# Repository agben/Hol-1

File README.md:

**HOL-1 a homebrew 8-bit TTL CPU**
---
HOL-1 is a TTL based 8-bit CPU based on the 'simple as possible' breadboard design by Ben Eater https://eater.net/8bit/

As well as adding my own modifications to each module of this CPU. i.e.
- more memory
- more registers
- more ALU functions
- more commands (assembler code to follow)

The main change is that HOL-1 is designed for permanent construction using common 8cm x 12cm double-sided perfboards.
  
For more on HOL-1 see www.benningtons.net  
  
**Design Principles**
---
- A working CPU is more important than performance or perfection (I'm learning as I go!)
- Using basic TTL 74LS family IC's from circa mid-70's. i.e. an ALU on one chip would be easier but where's the learning in that
- 8cm x 12cm double-sided perfboards = a 30 x 42 grid of 2.54mm spaced vias
- Initial design is on Fritzing (better suited to perfboard layouts but not suitable for Git)
- KiCad is then used for a more professional(ish) schematic and PCB design (and a more suitable format for Git)
- The KiCad PCB will adhere to the perfboard grid layout for component placement but tracks will then use a finer grid. This is because I'm not making PCBs but mass wiring the perfboard in wirewrapping style.
- Blinkenlights - plug-in status LEDs at every opportunity that could be swapped for control panel fly leads in the future

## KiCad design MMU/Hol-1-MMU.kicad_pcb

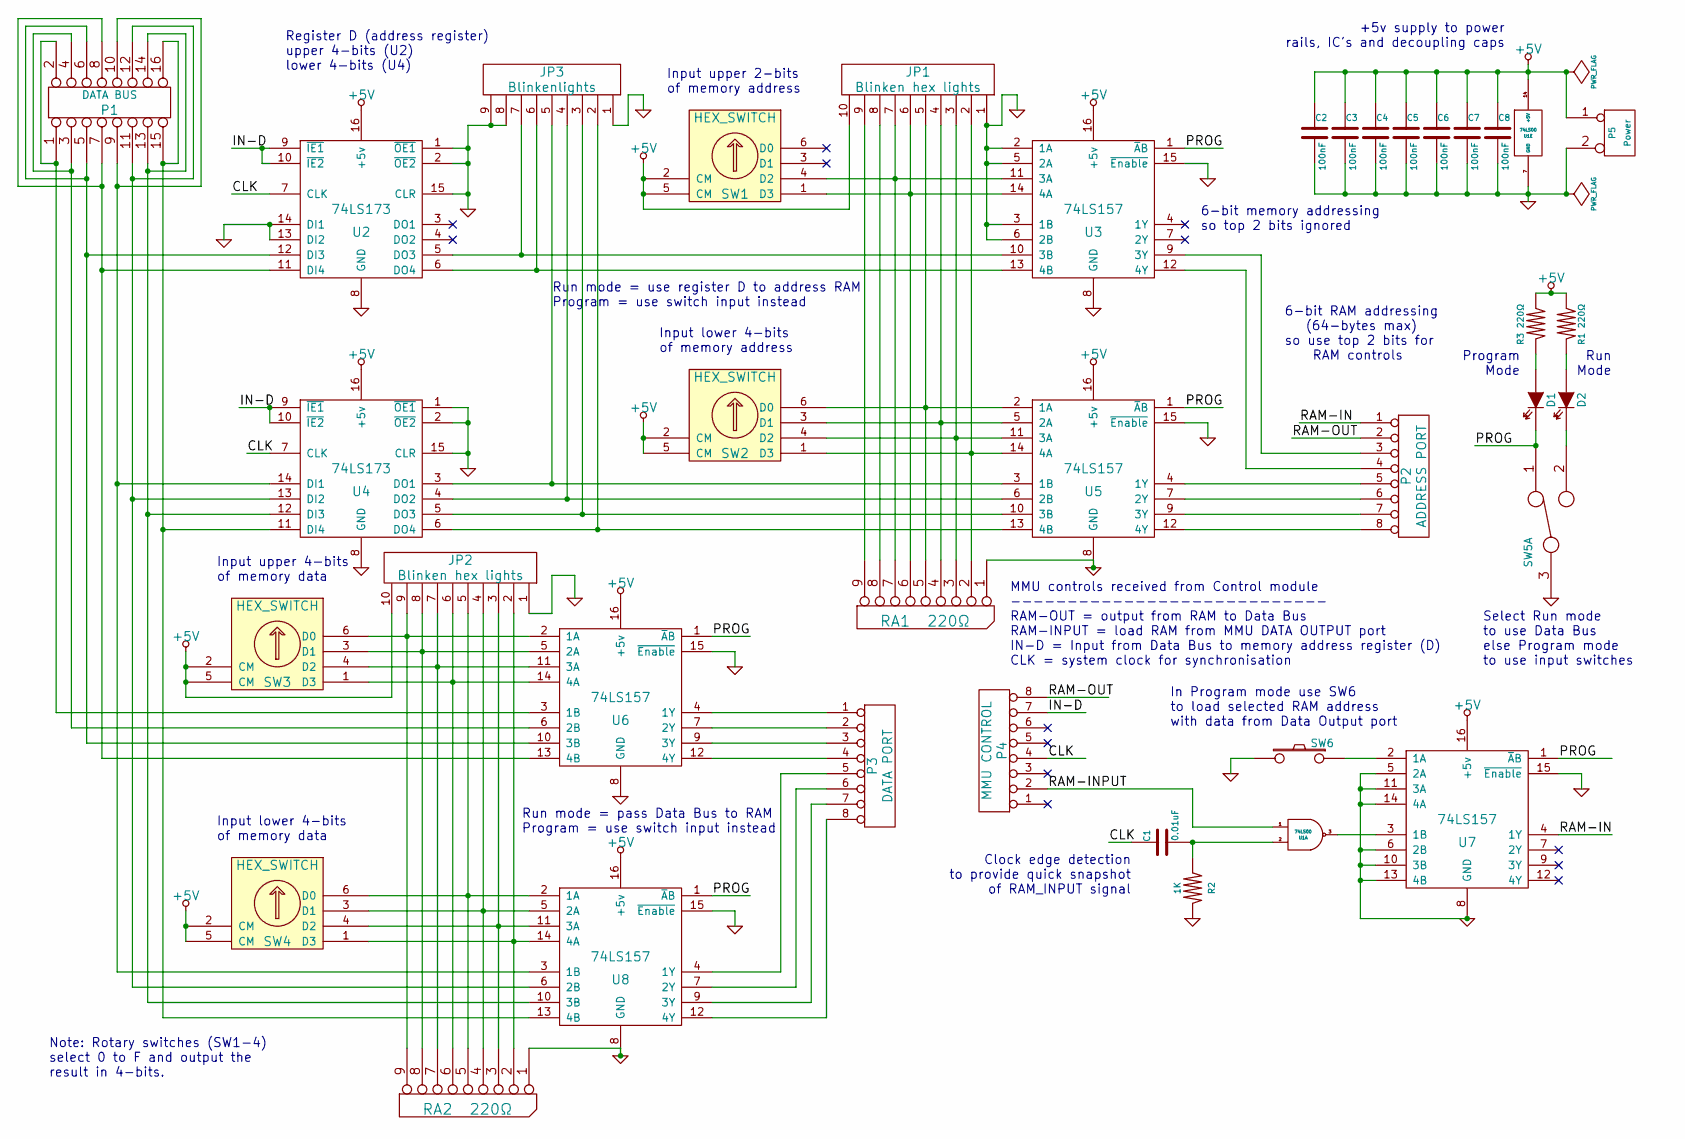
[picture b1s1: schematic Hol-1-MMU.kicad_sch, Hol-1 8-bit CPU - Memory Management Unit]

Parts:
C1: 0.01uF
C2, C3, C4, C5, C6, C7, C8: 100nF
D1, D2: LED
JP1, JP2: Blinken hex lights
JP3: Blinkenlights
P1: DATA BUS
P2: ADDRESS PORT
P3: DATA PORT
P4: MMU CONTROL
P5: Power
R1, R3: 220Ω
R2: 1K
RA1, RA2: 220Ω
SW1, SW2, SW3, SW4: HEX_SWITCH
SW5: DPDT
SW6: SW_PUSH
U1: 74LS00
U2, U4: 74LS173
U3, U5, U6, U7, U8: 74LS157

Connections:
+5V: C2.1, C3.1, C4.1, C5.1, C6.1, C7.1, C8.1, JP1.10, JP2.10, P5.1, R1.1, R3.1, SW1.2 (CM), SW1.5 (CM), SW2.2 (CM), SW2.5 (CM), SW3.2 (CM), SW3.5 (CM), SW4.2 (CM), SW4.5 (CM), U1.14 (+5V), U2.16 (+5v), U3.16 (+5v), U4.16 (+5v), U5.16 (+5v), U6.16 (+5v), U7.16 (+5v), U8.16 (+5v)
/CLK: C1.1, P4.4, U2.7 (CLK), U4.7 (CLK)
/IN-D: P4.7, U2.9 (~IE1), U2.10 (~IE2), U4.9 (~IE1), U4.10 (~IE2)
/PROG: D1.2 (K), SW5.1, U3.1 (~AB), U5.1 (~AB), U6.1 (~AB), U7.1 (~AB), U8.1 (~AB)
/RAM-IN: P2.1, U7.4 (1Y)
/RAM-INPUT: P4.2, U1.1
/RAM-OUT: P2.2, P4.8
GND: C2.2, C3.2, C4.2, C5.2, C6.2, C7.2, C8.2, JP1.1, JP2.1, JP3.1, JP3.8, JP3.9, P5.2 (PM), R2.2, RA1.1 (COM), RA2.1 (COM), SW5.3, SW6.2, U1.7 (GND), U2.1 (~OE1), U2.2 (~OE2), U2.8 (GND), U2.13 (DI2), U2.14 (DI1), U2.15 (CLR), U3.2 (1A), U3.3 (1B), U3.5 (2A), U3.6 (2B), U3.8 (GND), U3.15 (~Enable), U4.1 (~OE1), U4.2 (~OE2), U4.8 (GND), U4.15 (CLR), U5.8 (GND), U5.15 (~Enable), U6.8 (GND), U6.15 (~Enable), U7.5 (2A), U7.6 (2B), U7.8 (GND), U7.10 (3B), U7.11 (3A), U7.13 (4B), U7.14 (4A), U7.15 (~Enable), U8.8 (GND), U8.15 (~Enable)
unnamed: P2.4, U3.12 (4Y)
unnamed: P2.3, U3.9 (3Y)
unnamed: P1.1, P1.2, U6.3 (1B)
unnamed: P2.5, U5.4 (1Y)
unnamed: D2.2 (K), SW5.2
unnamed: JP2.2, RA2.2, SW4.1 (D3), U8.14 (4A)
unnamed: D1.1 (A), R3.2
unnamed: D2.1 (A), R1.2
unnamed: P2.8, U5.12 (4Y)
unnamed: P2.7, U5.9 (3Y)
unnamed: P2.6, U5.7 (2Y)
unnamed: P3.4, U6.12 (4Y)
unnamed: P3.3, U6.9 (3Y)
unnamed: P3.2, U6.7 (2Y)
unnamed: P1.3, P1.4, U6.6 (2B)
unnamed: JP2.7, RA2.7, SW3.4 (D2), U6.11 (3A)
unnamed: JP2.3, RA2.3, SW4.4 (D2), U8.11 (3A)
unnamed: JP2.4, RA2.4, SW4.3 (D1), U8.5 (2A)
unnamed: JP2.5, RA2.5, SW4.6 (D0), U8.2 (1A)
unnamed: JP2.6, RA2.6, SW3.1 (D3), U6.14 (4A)
unnamed: JP2.8, RA2.8, SW3.3 (D1), U6.5 (2A)
unnamed: JP2.9, RA2.9, SW3.6 (D0), U6.2 (1A)
unnamed: P3.1, U6.4 (1Y)
unnamed: JP3.3, U4.5 (DO3), U5.10 (3B)
unnamed: JP1.8, RA1.8
unnamed: JP1.9, RA1.9
unnamed: JP3.4, U4.4 (DO2), U5.6 (2B)
unnamed: JP3.5, U4.3 (DO1), U5.3 (1B)
unnamed: JP3.6, U2.6 (DO4), U3.13 (4B)
unnamed: JP3.7, U2.5 (DO3), U3.10 (3B)
unnamed: P1.15, P1.16, U4.11 (DI4), U8.13 (4B)
unnamed: P1.13, P1.14, U4.12 (DI3), U8.10 (3B)
unnamed: P1.11, P1.12, U4.13 (DI2), U8.6 (2B)
unnamed: P1.9, P1.10, U4.14 (DI1), U8.3 (1B)
unnamed: JP1.7, RA1.7, SW1.4 (D2), U3.11 (3A)
unnamed: JP1.2, RA1.2, SW2.1 (D3), U5.14 (4A)
unnamed: JP1.3, RA1.3, SW2.4 (D2), U5.11 (3A)
unnamed: JP1.4, RA1.4, SW2.3 (D1), U5.5 (2A)
unnamed: JP1.5, RA1.5, SW2.6 (D0), U5.2 (1A)
unnamed: JP1.6, RA1.6, SW1.1 (D3), U3.14 (4A)
unnamed: JP3.2, U4.6 (DO4), U5.13 (4B)
unnamed: P1.7, P1.8, U2.11 (DI4), U6.13 (4B)
unnamed: P1.5, P1.6, U2.12 (DI3), U6.10 (3B)
unnamed: P3.5, U8.4 (1Y)
unnamed: P3.6, U8.7 (2Y)
unnamed: P3.7, U8.9 (3Y)
unnamed: P3.8, U8.12 (4Y)
unnamed: SW6.1, U7.2 (1A)
unnamed: U1.3, U7.3 (1B)
unnamed: C1.2, R2.1, U1.2

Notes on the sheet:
Select Run mode to use Data Bus else Program mode to use input switches
6-bit memory addressing so top 2 bits ignored
Run mode = pass Data Bus to RAM Program = use switch input instead
Note: Rotary switches (SW1-4) select 0 to F and output the result in 4-bits.
Clock edge detection to provide quick snapshot of RAM_INPUT signal
Register D (address register) upper 4-bits (U2) lower 4-bits (U4)
Run mode = use register D to address RAM Program = use switch input instead
Input lower 4-bits of memory address
MMU controls received from Control module ---------------------------- RAM-OUT = output from RAM to Data Bus RAM-INPUT = load RAM from MMU DATA OUTPUT port IN-D = Input from Data Bus to memory address register (D) CLK = system clock for synchronisation
Input lower 4-bits of memory data
Input upper 2-bits of memory address
+5v supply to power rails, IC's and decoupling caps
Run Mode
In Program mode use SW6 to load selected RAM address with data from Data Output port
Program Mode
Input upper 4-bits of memory data
6-bit RAM addressing (64-bytes max) so use top 2 bits for RAM controls

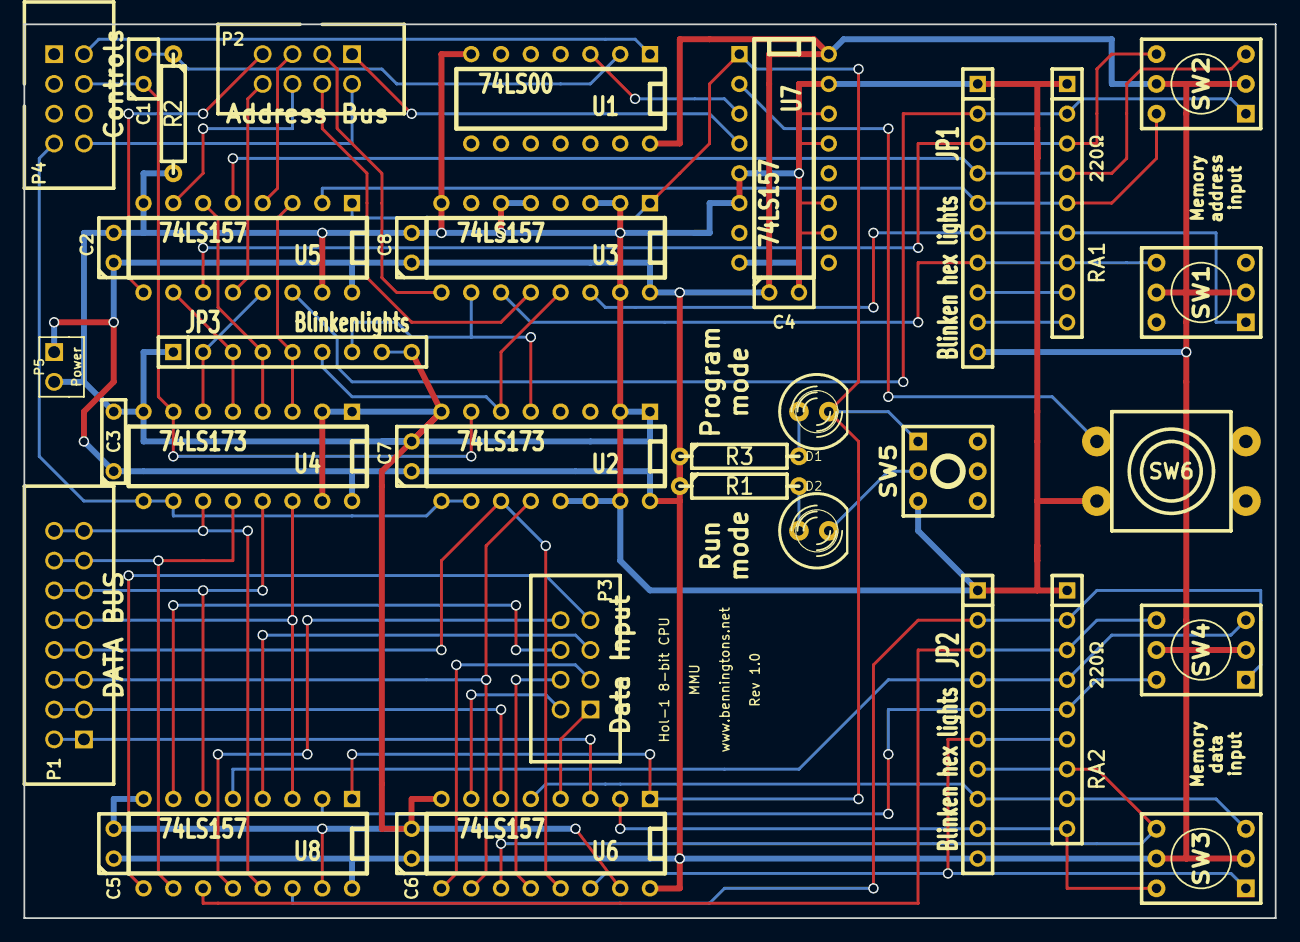
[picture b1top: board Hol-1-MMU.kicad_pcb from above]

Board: 2 copper layers, 106.7 x 76.2 mm, 37 parts (0 on the bottom side), 58 nets.

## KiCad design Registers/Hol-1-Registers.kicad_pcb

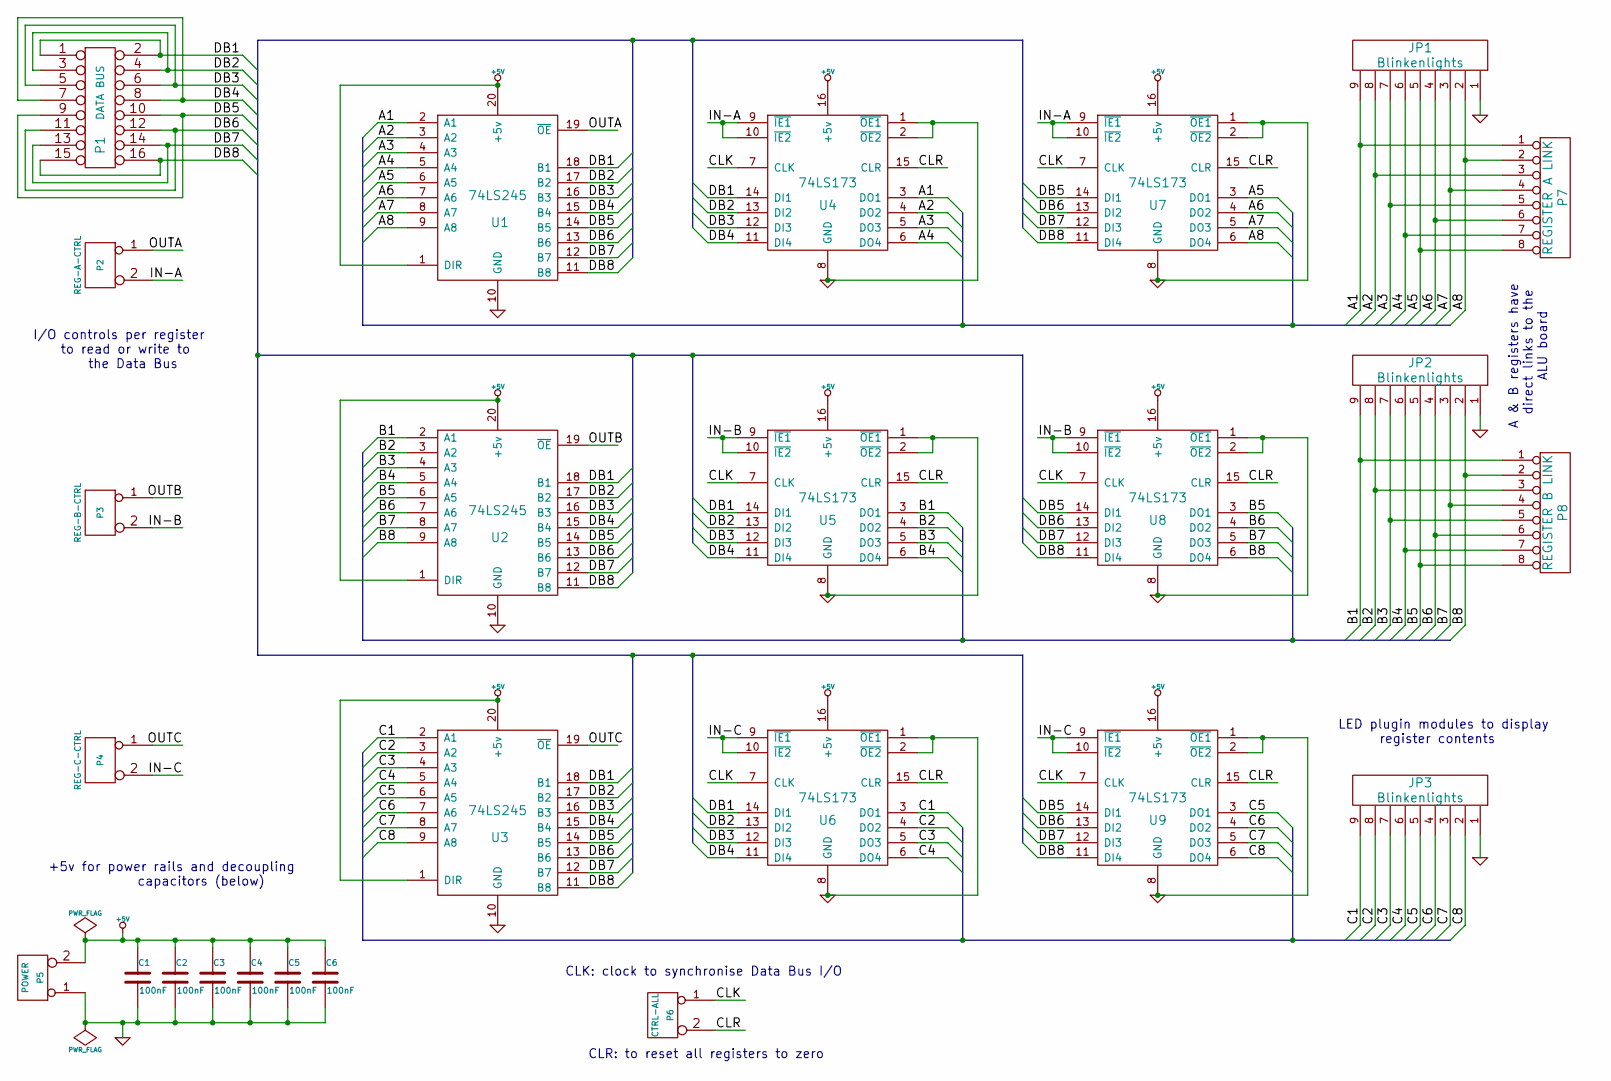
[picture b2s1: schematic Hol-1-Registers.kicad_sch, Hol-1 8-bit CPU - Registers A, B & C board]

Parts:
C1, C2, C3, C4, C5, C6: 100nF
JP1, JP2, JP3: Blinkenlights
P1: DATA BUS
P2: REG-A-CTRL
P3: REG-B-CTRL
P4: REG-C-CTRL
P5: POWER
P6: CTRL-ALL
P7: REGISTER A LINK
P8: REGISTER B LINK
U1, U2, U3: 74LS245
U4, U5, U6, U7, U8, U9: 74LS173

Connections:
+5V: C1.1, C2.1, C3.1, C4.1, C5.1, C6.1, P5.2 (PM), U1.1 (DIR), U1.20 (+5v), U2.1 (DIR), U2.20 (+5v), U3.1 (DIR), U3.20 (+5v), U4.16 (+5v), U5.16 (+5v), U6.16 (+5v), U7.16 (+5v), U8.16 (+5v), U9.16 (+5v)
/A1: JP1.9, P7.1, U1.2 (A1), U4.3 (DO1)
/A2: JP1.8, P7.3, U1.3 (A2), U4.4 (DO2)
/A3: JP1.7, P7.5, U1.4 (A3), U4.5 (DO3)
/A4: JP1.6, P7.7, U1.5 (A4), U4.6 (DO4)
/A5: JP1.5, P7.8, U1.6 (A5), U7.3 (DO1)
/A6: JP1.4, P7.6, U1.7 (A6), U7.4 (DO2)
/A7: JP1.3, P7.4, U1.8 (A7), U7.5 (DO3)
/A8: JP1.2, P7.2, U1.9 (A8), U7.6 (DO4)
/B1: JP2.9, P8.1, U2.2 (A1), U5.3 (DO1)
/B2: JP2.8, P8.3, U2.3 (A2), U5.4 (DO2)
/B3: JP2.7, P8.5, U2.4 (A3), U5.5 (DO3)
/B4: JP2.6, P8.7, U2.5 (A4), U5.6 (DO4)
/B5: JP2.5, P8.8, U2.6 (A5), U8.3 (DO1)
/B6: JP2.4, P8.6, U2.7 (A6), U8.4 (DO2)
/B7: JP2.3, P8.4, U2.8 (A7), U8.5 (DO3)
/B8: JP2.2, P8.2, U2.9 (A8), U8.6 (DO4)
/C1: JP3.9, U3.2 (A1), U6.3 (DO1)
/C2: JP3.8, U3.3 (A2), U6.4 (DO2)
/C3: JP3.7, U3.4 (A3), U6.5 (DO3)
/C4: JP3.6, U3.5 (A4), U6.6 (DO4)
/C5: JP3.5, U3.6 (A5), U9.3 (DO1)
/C6: JP3.4, U3.7 (A6), U9.4 (DO2)
/C7: JP3.3, U3.8 (A7), U9.5 (DO3)
/C8: JP3.2, U3.9 (A8), U9.6 (DO4)
/CLK: P6.1, U4.7 (CLK), U5.7 (CLK), U6.7 (CLK), U7.7 (CLK), U8.7 (CLK), U9.7 (CLK)
/CLR: P6.2 (PM), U4.15 (CLR), U5.15 (CLR), U6.15 (CLR), U7.15 (CLR), U8.15 (CLR), U9.15 (CLR)
/DB1: P1.1, P1.2, U1.18 (B1), U2.18 (B1), U3.18 (B1), U4.14 (DI1), U5.14 (DI1), U6.14 (DI1)
/DB2: P1.3, P1.4, U1.17 (B2), U2.17 (B2), U3.17 (B2), U4.13 (DI2), U5.13 (DI2), U6.13 (DI2)
/DB3: P1.5, P1.6, U1.16 (B3), U2.16 (B3), U3.16 (B3), U4.12 (DI3), U5.12 (DI3), U6.12 (DI3)
/DB4: P1.7, P1.8, U1.15 (B4), U2.15 (B4), U3.15 (B4), U4.11 (DI4), U5.11 (DI4), U6.11 (DI4)
/DB5: P1.9, P1.10, U1.14 (B5), U2.14 (B5), U3.14 (B5), U7.14 (DI1), U8.14 (DI1), U9.14 (DI1)
/DB6: P1.11, P1.12, U1.13 (B6), U2.13 (B6), U3.13 (B6), U7.13 (DI2), U8.13 (DI2), U9.13 (DI2)
/DB7: P1.13, P1.14, U1.12 (B7), U2.12 (B7), U3.12 (B7), U7.12 (DI3), U8.12 (DI3), U9.12 (DI3)
/DB8: P1.15, P1.16, U1.11 (B8), U2.11 (B8), U3.11 (B8), U7.11 (DI4), U8.11 (DI4), U9.11 (DI4)
/IN-A: P2.2 (PM), U4.9 (~IE1), U4.10 (~IE2), U7.9 (~IE1), U7.10 (~IE2)
/IN-B: P3.2 (PM), U5.9 (~IE1), U5.10 (~IE2), U8.9 (~IE1), U8.10 (~IE2)
/IN-C: P4.2 (PM), U6.9 (~IE1), U6.10 (~IE2), U9.9 (~IE1), U9.10 (~IE2)
/OUTA: P2.1, U1.19 (~OE)
/OUTB: P3.1, U2.19 (~OE)
/OUTC: P4.1, U3.19 (~OE)
GND: C1.2, C2.2, C3.2, C4.2, C5.2, C6.2, JP1.1, JP2.1, JP3.1, P5.1, U1.10 (GND), U2.10 (GND), U3.10 (GND), U4.1 (~OE1), U4.2 (~OE2), U4.8 (GND), U5.1 (~OE1), U5.2 (~OE2), U5.8 (GND), U6.1 (~OE1), U6.2 (~OE2), U6.8 (GND), U7.1 (~OE1), U7.2 (~OE2), U7.8 (GND), U8.1 (~OE1), U8.2 (~OE2), U8.8 (GND), U9.1 (~OE1), U9.2 (~OE2), U9.8 (GND)

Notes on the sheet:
CLR: to reset all registers to zero
A & B registers have direct links to the ALU board
CLK: clock to synchronise Data Bus I/O
+5v for power rails and decoupling capacitors (below)
LED plugin modules to display register contents
I/O controls per register to read or write to the Data Bus

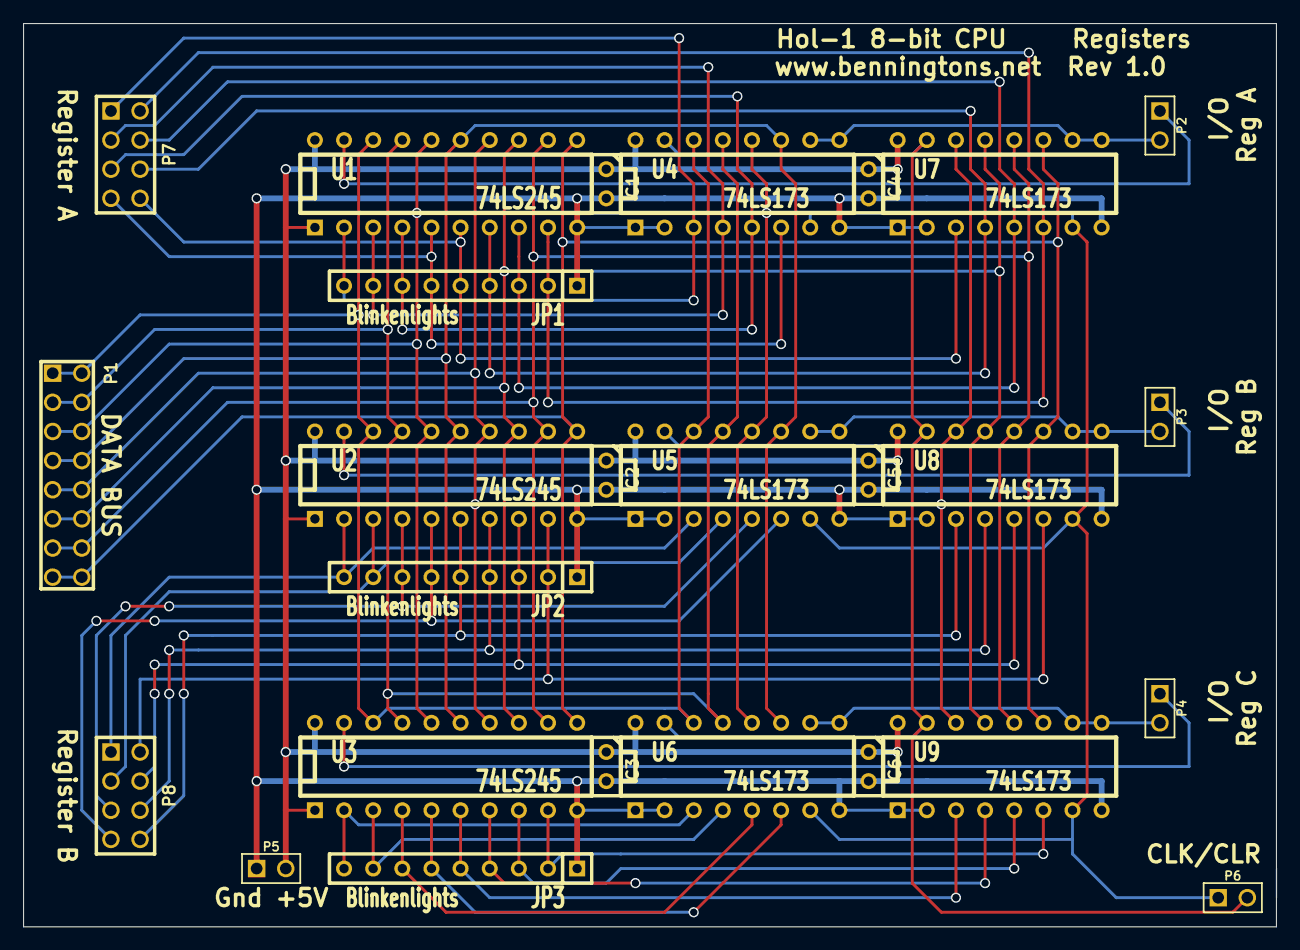
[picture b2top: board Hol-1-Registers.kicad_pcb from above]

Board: 2 copper layers, 109.2 x 78.7 mm, 26 parts (0 on the bottom side), 42 nets.

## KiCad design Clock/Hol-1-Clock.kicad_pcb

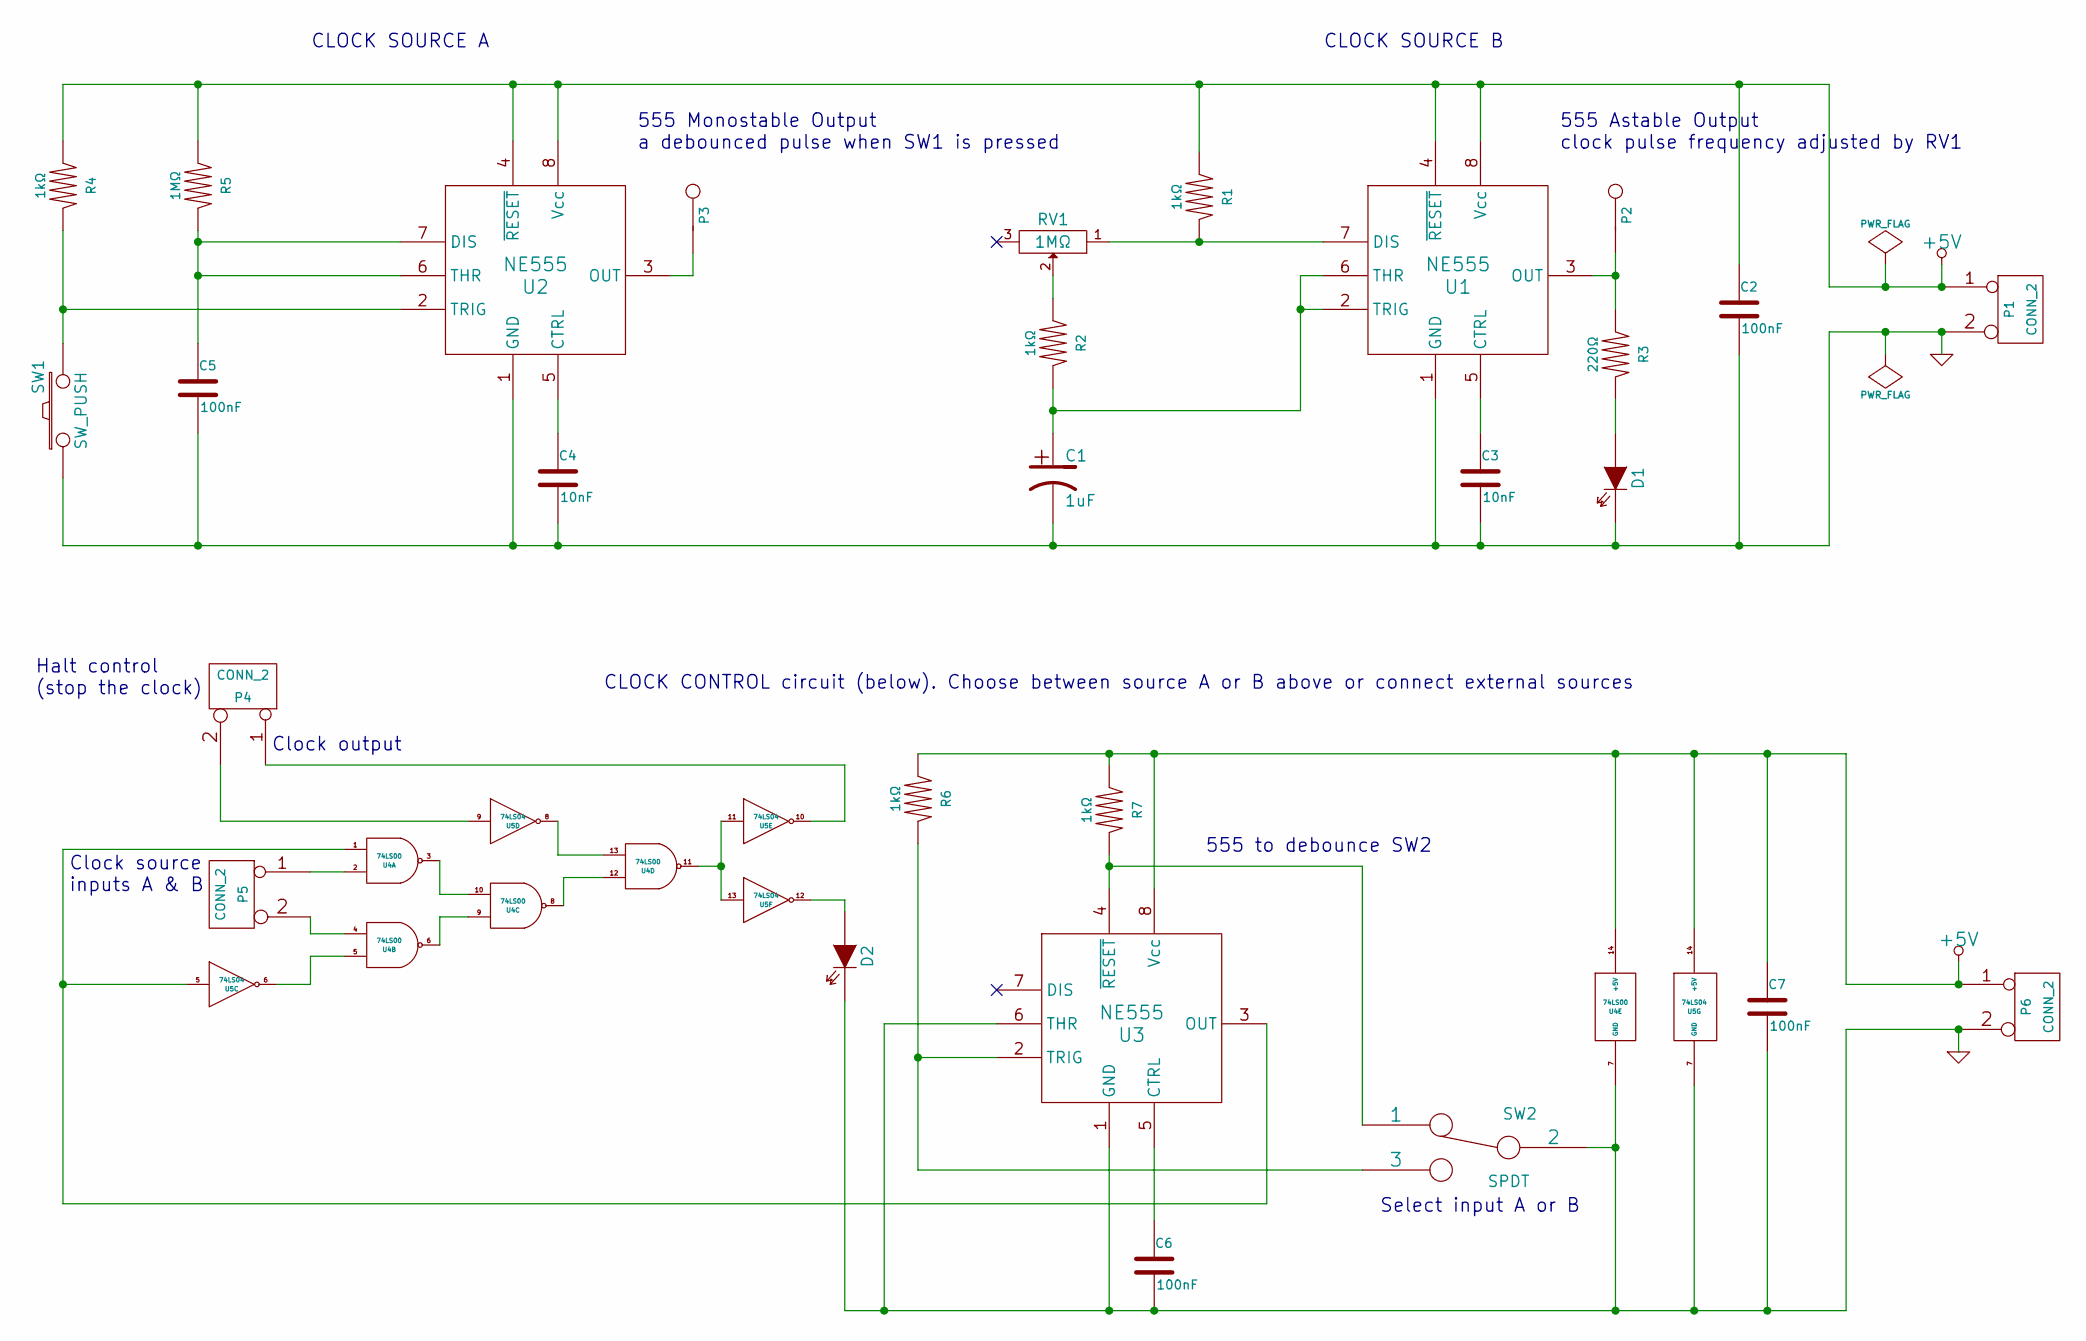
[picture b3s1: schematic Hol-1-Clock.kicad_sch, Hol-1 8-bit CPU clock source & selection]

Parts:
C1: 1uF
C2, C5, C6, C7: 100nF
C3, C4: 10nF
D1, D2: LED
P1, P4, P5, P6: CONN_2
P2, P3: CONN_1
R1, R2, R4, R6, R7: 1kΩ
R3: 220Ω
R5: 1MΩ
RV1: 1MΩ
SW1: SW_PUSH
SW2: SPDT
U1, U2, U3: NE555
U4: 74LS00
U5: 74LS04

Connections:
+5V: C2.1, C7.1, P1.1, P6.1, R1.1, R4.1, R5.1, R6.1, R7.1, U1.4 (~RESET), U1.8 (Vcc), U2.4 (~RESET), U2.8 (Vcc), U3.8 (Vcc), U4.14 (+5V), U5.14 (+5V)
GND: C1.2, C2.2, C3.2, C4.2, C5.2, C6.2, C7.2, D1.2 (K), D2.2 (K), P1.2 (PM), P6.2 (PM), SW1.1, SW2.2, U1.1 (GND), U2.1 (GND), U3.1 (GND), U3.6 (THR), U4.7 (GND), U5.7 (GND)
unnamed: C5.1, R5.2, U2.6 (THR), U2.7 (DIS)
unnamed: R4.2, SW1.2, U2.2 (TRIG)
unnamed: C6.1, U3.5 (CTRL)
unnamed: D1.1 (A), R3.2
unnamed: P2.1, R3.1, U1.3 (OUT)
unnamed: C3.1, U1.5 (CTRL)
unnamed: R2.1, RV1.2
unnamed: P3.1, U2.3 (OUT)
unnamed: C4.1, U2.5 (CTRL)
unnamed: P5.2 (PM), U4.4
unnamed: U4.5, U5.6
unnamed: P4.2 (PM), U5.9
unnamed: R7.2, SW2.1, U3.4 (~RESET)
unnamed: P5.1, U4.2
unnamed: D2.1 (A), U5.12
unnamed: P4.1, U5.10
unnamed: U4.11, U5.11, U5.13
unnamed: R6.2, SW2.3, U3.2 (TRIG)
unnamed: U4.13, U5.8
unnamed: U4.8, U4.12
unnamed: U4.3, U4.10
unnamed: U4.6, U4.9
unnamed: U3.3 (OUT), U4.1, U5.5
unnamed: R1.2, RV1.1, U1.7 (DIS)
unnamed: C1.1, R2.2, U1.2 (TRIG), U1.6 (THR)

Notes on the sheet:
Select input A or B
CLOCK SOURCE A
CLOCK SOURCE B
555 Monostable Output a debounced pulse when SW1 is pressed
555 Astable Output clock pulse frequency adjusted by RV1
Halt control (stop the clock)
CLOCK CONTROL circuit (below). Choose between source A or B above or connect external sources
555 to debounce SW2
Clock source inputs A & B
Clock output

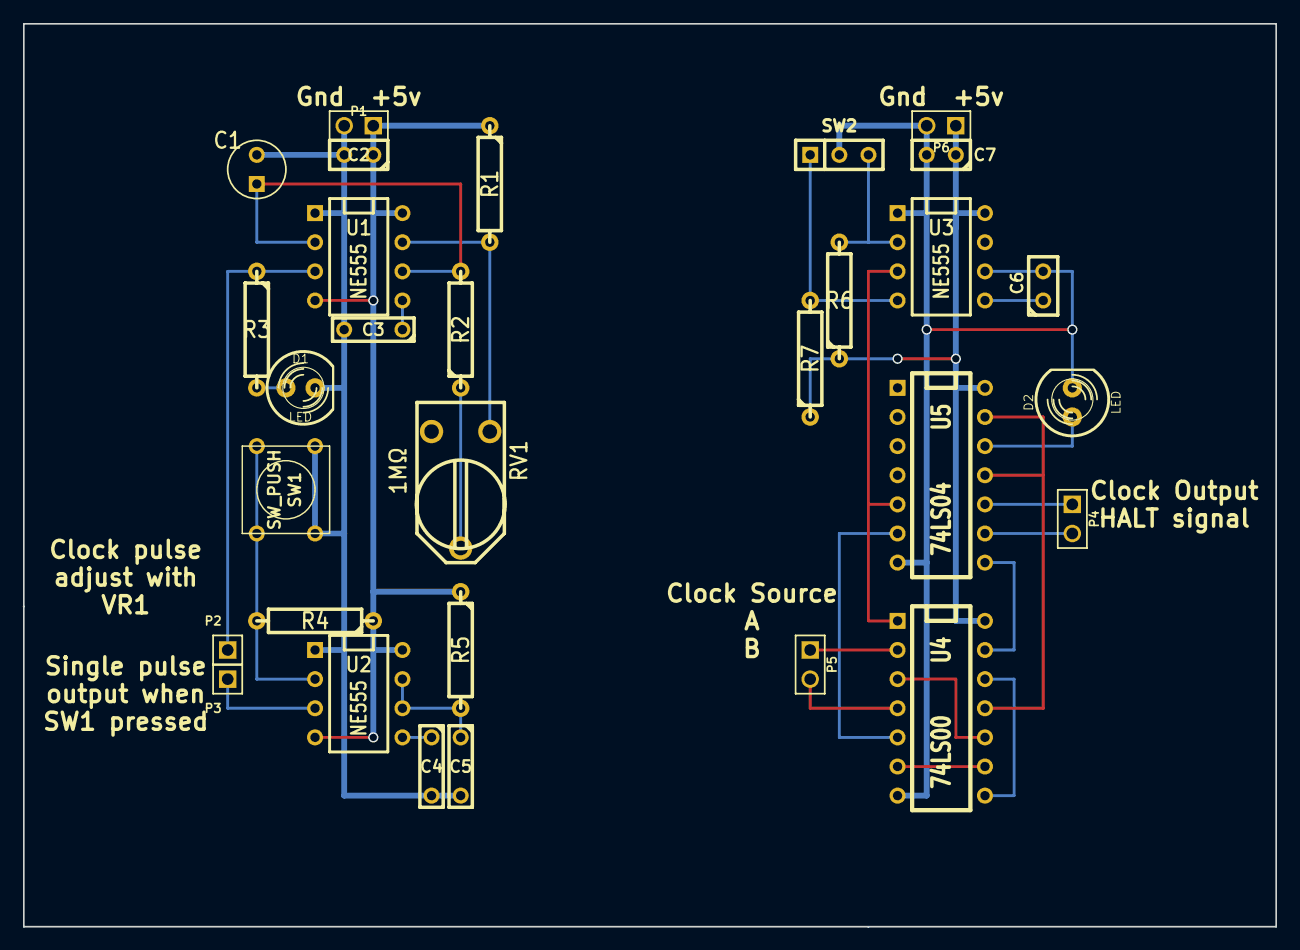
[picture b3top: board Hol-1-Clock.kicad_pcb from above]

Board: 2 copper layers, 109.2 x 78.7 mm, 30 parts (0 on the bottom side), 27 nets.

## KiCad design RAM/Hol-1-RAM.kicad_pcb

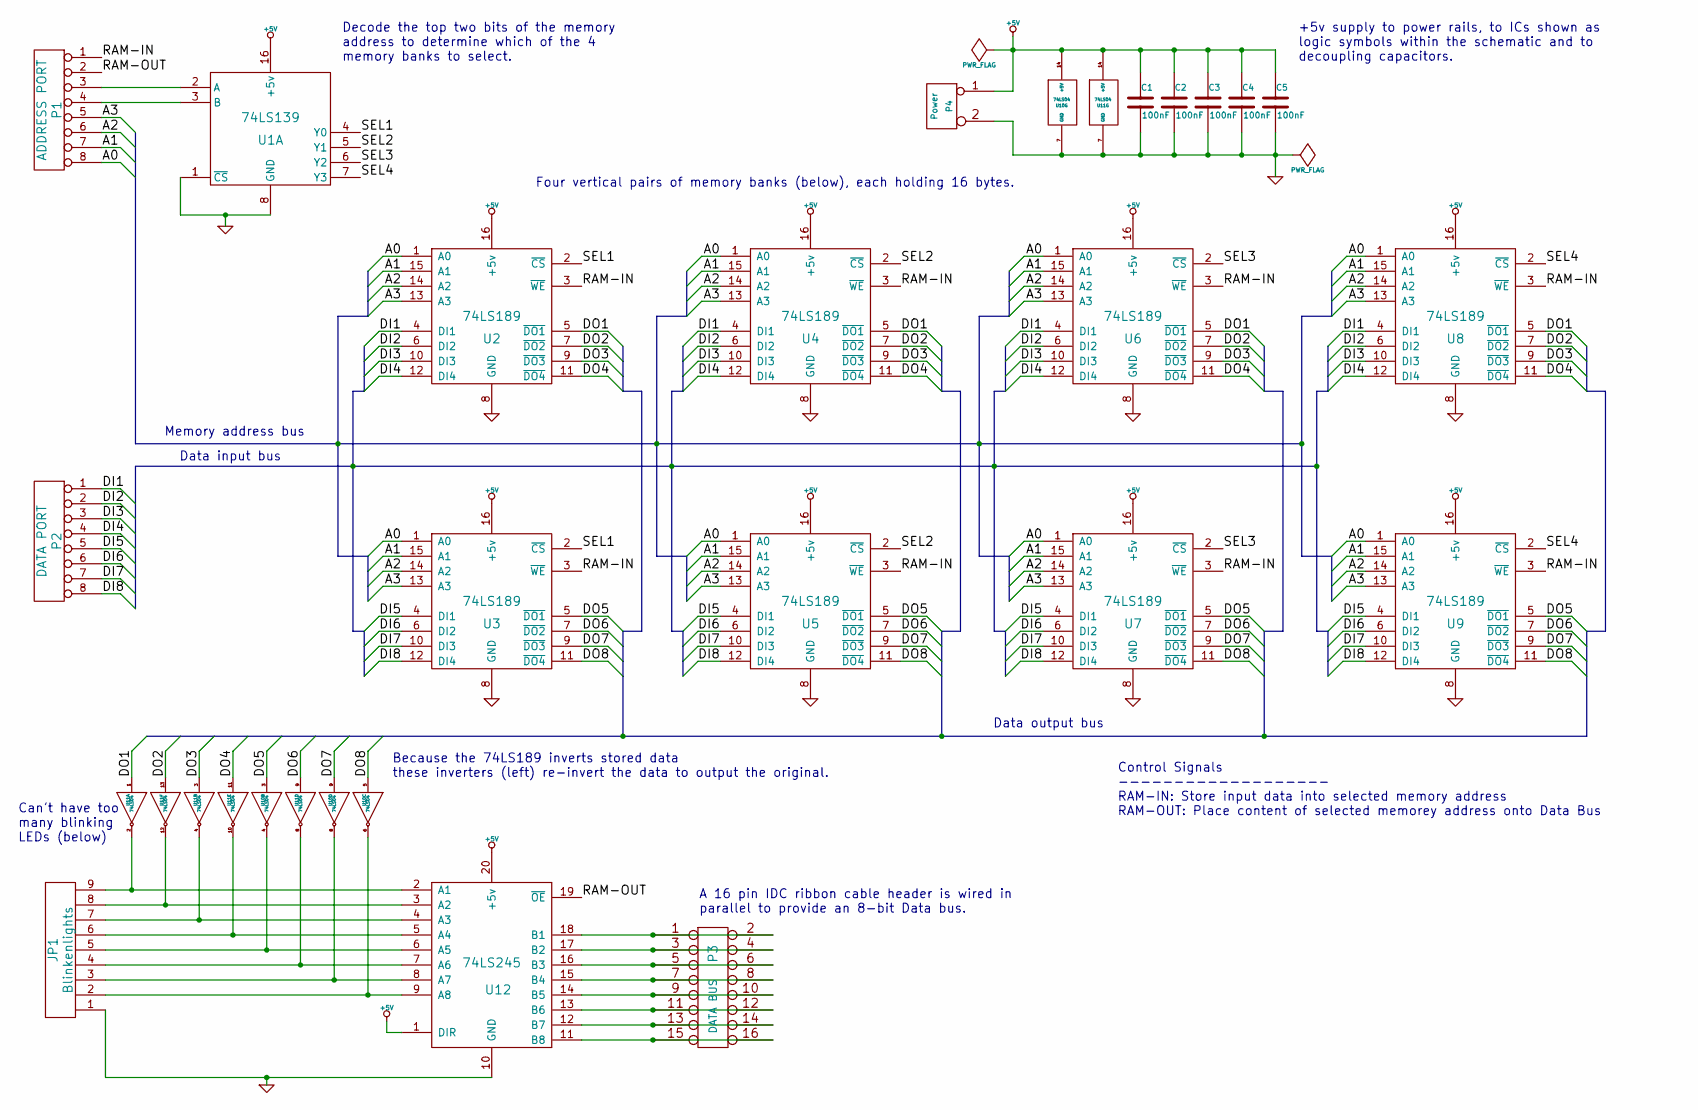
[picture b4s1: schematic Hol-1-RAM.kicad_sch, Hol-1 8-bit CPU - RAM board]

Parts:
C1, C2, C3, C4, C5: 100nF
JP1: Blinkenlights
P1: ADDRESS PORT
P2: DATA PORT
P3: DATA BUS
P4: Power
U1: 74LS139
U2, U3, U4, U5, U6, U7, U8, U9: 74LS189
U10, U11: 74LS04
U12: 74LS245

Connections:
+5V: C1.1, C2.1, C3.1, C4.1, C5.1, P4.1, U1.16 (+5v), U2.16 (+5v), U3.16 (+5v), U4.16 (+5v), U5.16 (+5v), U6.16 (+5v), U7.16 (+5v), U8.16 (+5v), U9.16 (+5v), U10.14 (+5V), U11.14 (+5V), U12.1 (DIR), U12.20 (+5v)
/A0: P1.8, U2.1 (A0), U3.1 (A0), U4.1 (A0), U5.1 (A0), U6.1 (A0), U7.1 (A0), U8.1 (A0), U9.1 (A0)
/A1: P1.7, U2.15 (A1), U3.15 (A1), U4.15 (A1), U5.15 (A1), U6.15 (A1), U7.15 (A1), U8.15 (A1), U9.15 (A1)
/A2: P1.6, U2.14 (A2), U3.14 (A2), U4.14 (A2), U5.14 (A2), U6.14 (A2), U7.14 (A2), U8.14 (A2), U9.14 (A2)
/A3: P1.5, U2.13 (A3), U3.13 (A3), U4.13 (A3), U5.13 (A3), U6.13 (A3), U7.13 (A3), U8.13 (A3), U9.13 (A3)
/DI1: P2.1, U2.4 (DI1), U4.4 (DI1), U6.4 (DI1), U8.4 (DI1)
/DI2: P2.2, U2.6 (DI2), U4.6 (DI2), U6.6 (DI2), U8.6 (DI2)
/DI3: P2.3, U2.10 (DI3), U4.10 (DI3), U6.10 (DI3), U8.10 (DI3)
/DI4: P2.4, U2.12 (DI4), U4.12 (DI4), U6.12 (DI4), U8.12 (DI4)
/DI5: P2.5, U3.4 (DI1), U5.4 (DI1), U7.4 (DI1), U9.4 (DI1)
/DI6: P2.6, U3.6 (DI2), U5.6 (DI2), U7.6 (DI2), U9.6 (DI2)
/DI7: P2.7, U3.10 (DI3), U5.10 (DI3), U7.10 (DI3), U9.10 (DI3)
/DI8: P2.8, U3.12 (DI4), U5.12 (DI4), U7.12 (DI4), U9.12 (DI4)
/DO1: U2.5 (~DO1), U4.5 (~DO1), U6.5 (~DO1), U8.5 (~DO1), U11.1
/DO2: U2.7 (~DO2), U4.7 (~DO2), U6.7 (~DO2), U8.7 (~DO2), U11.13
/DO3: U2.9 (~DO3), U4.9 (~DO3), U6.9 (~DO3), U8.9 (~DO3), U11.3
/DO4: U2.11 (~DO4), U4.11 (~DO4), U6.11 (~DO4), U8.11 (~DO4), U11.11
/DO5: U3.5 (~DO1), U5.5 (~DO1), U7.5 (~DO1), U9.5 (~DO1), U10.3
/DO6: U3.7 (~DO2), U5.7 (~DO2), U7.7 (~DO2), U9.7 (~DO2), U11.9
/DO7: U3.9 (~DO3), U5.9 (~DO3), U7.9 (~DO3), U9.9 (~DO3), U10.9
/DO8: U3.11 (~DO4), U5.11 (~DO4), U7.11 (~DO4), U9.11 (~DO4), U10.5
/RAM-IN: P1.1, U2.3 (~WE), U3.3 (~WE), U4.3 (~WE), U5.3 (~WE), U6.3 (~WE), U7.3 (~WE), U8.3 (~WE), U9.3 (~WE)
/RAM-OUT: P1.2, U12.19 (~OE)
/SEL1: U1.4 (Y0), U2.2 (~CS), U3.2 (~CS)
/SEL2: U1.5 (Y1), U4.2 (~CS), U5.2 (~CS)
/SEL3: U1.6 (Y2), U6.2 (~CS), U7.2 (~CS)
/SEL4: U1.7 (Y3), U8.2 (~CS), U9.2 (~CS)
GND: C1.2, C2.2, C3.2, C4.2, C5.2, JP1.1, P4.2 (PM), U1.1 (~CS), U1.8 (GND), U2.8 (GND), U3.8 (GND), U4.8 (GND), U5.8 (GND), U6.8 (GND), U7.8 (GND), U8.8 (GND), U9.8 (GND), U10.7 (GND), U11.7 (GND), U12.10 (GND)
unnamed: JP1.5, U10.4, U12.6 (A5)
unnamed: JP1.4, U11.8, U12.7 (A6)
unnamed: JP1.3, U10.8, U12.8 (A7)
unnamed: JP1.2, U10.6, U12.9 (A8)
unnamed: JP1.6, U11.10, U12.5 (A4)
unnamed: JP1.7, U11.4, U12.4 (A3)
unnamed: JP1.8, U11.12, U12.3 (A2)
unnamed: JP1.9, U11.2, U12.2 (A1)
unnamed: P3.9, P3.10, U12.14 (B5)
unnamed: P3.11, P3.12, U12.13 (B6)
unnamed: P3.13, P3.14, U12.12 (B7)
unnamed: P3.15, P3.16, U12.11 (B8)
unnamed: P3.7, P3.8, U12.15 (B4)
unnamed: P1.3, U1.2 (A)
unnamed: P1.4, U1.3 (B)
unnamed: P3.1, P3.2, U12.18 (B1)
unnamed: P3.3, P3.4, U12.17 (B2)
unnamed: P3.5, P3.6, U12.16 (B3)

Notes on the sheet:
Decode the top two bits of the memory address to determine which of the 4 memory banks to select.
Data input bus
A 16 pin IDC ribbon cable header is wired in parallel to provide an 8-bit Data bus.
Memory address bus
Data output bus
Four vertical pairs of memory banks (below), each holding 16 bytes.
Because the 74LS189 inverts stored data these inverters (left) re-invert the data to output the original.
Control Signals ------------------- RAM-IN: Store input data into selected memory address RAM-OUT: Place content of selected memorey address onto Data Bus
+5v supply to power rails, to ICs shown as logic symbols within the schematic and to decoupling capacitors.
Can't have too many blinking LEDs (below)

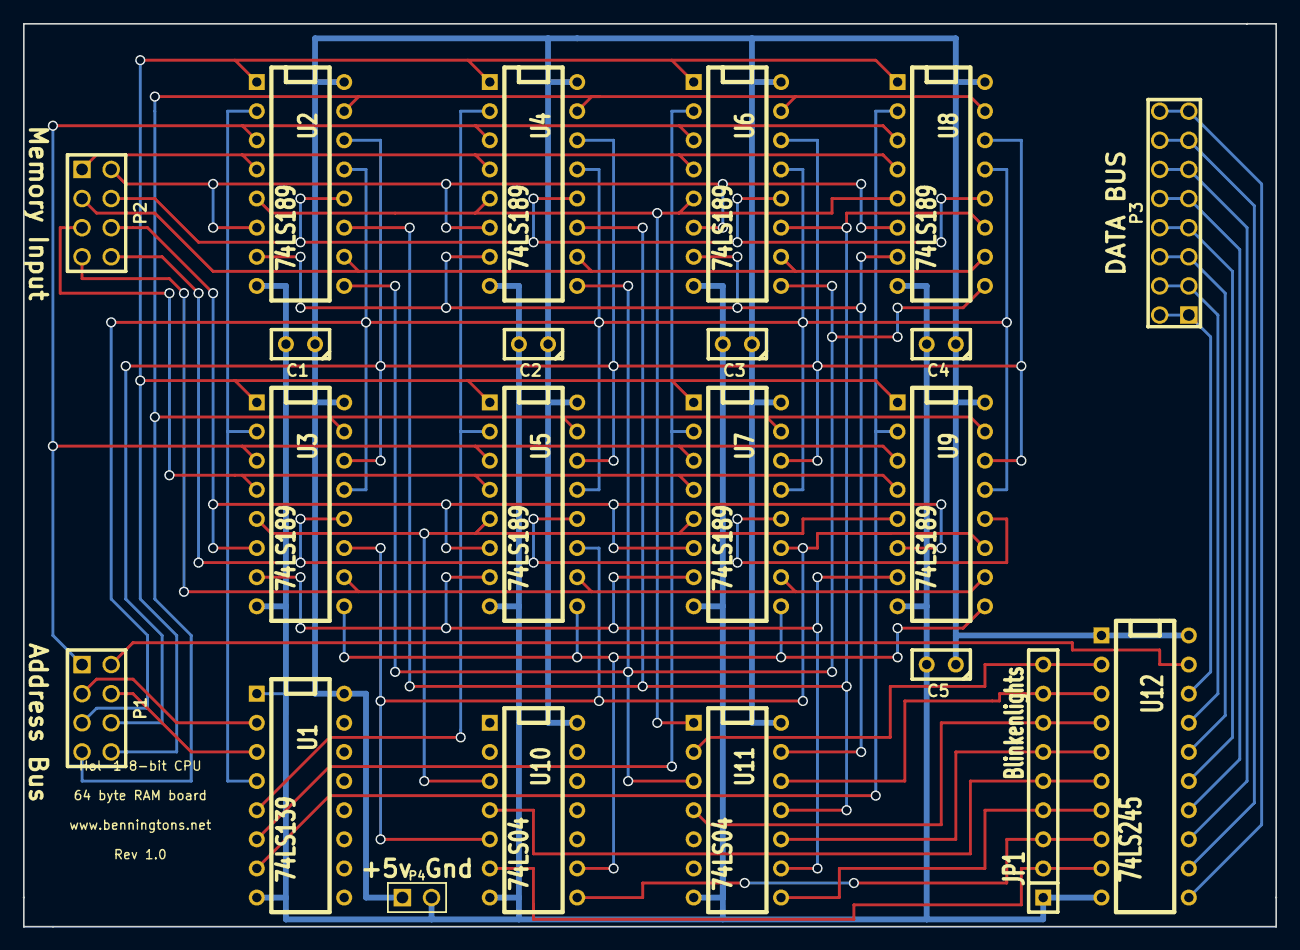
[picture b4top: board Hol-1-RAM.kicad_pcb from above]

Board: 2 copper layers, 109.2 x 78.7 mm, 22 parts (0 on the bottom side), 46 nets.
